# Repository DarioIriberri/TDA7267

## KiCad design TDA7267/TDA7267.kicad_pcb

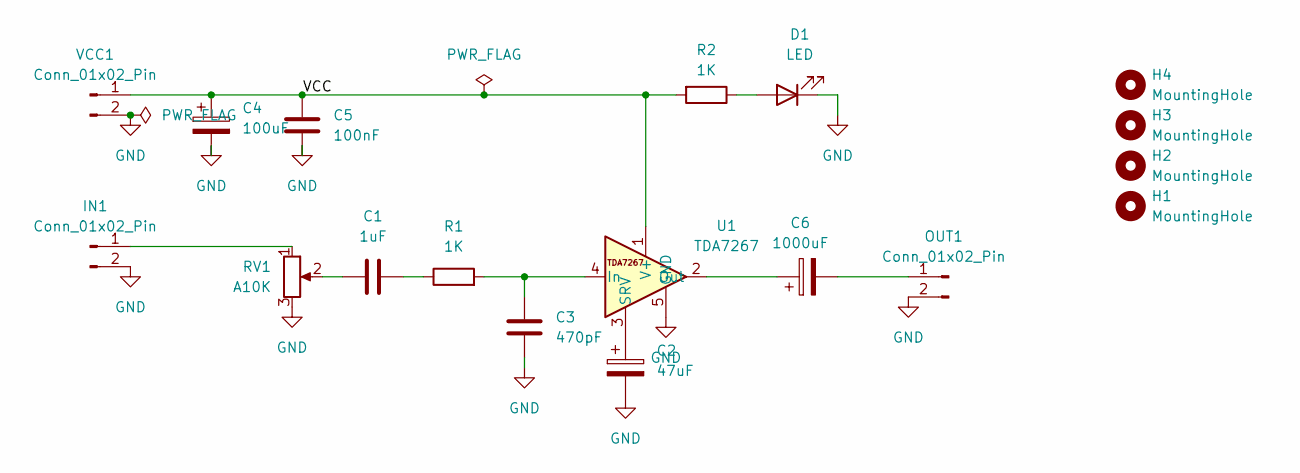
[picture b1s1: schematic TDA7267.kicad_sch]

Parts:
C1: 1uF; C_Rect_L7.2mm_W3.5mm_P5.00mm_FKS2_FKP2_MKS2_MKP2
C2: 47uF; CP_Radial_D8.0mm_P3.80mm
C3: 470pF; C_Disc_D6.0mm_W2.5mm_P5.00mm
C4: 100uF; CP_Radial_D8.0mm_P3.80mm
C5: 100nF; C_Disc_D6.0mm_W2.5mm_P5.00mm
C6: 1000uF; CP_Radial_D10.0mm_P5.00mm
D1: LED; LED_D5.0mm
H1, H2, H3, H4: MountingHole; MountingHole_2.2mm_M2
IN1: Conn_01x02_Pin; TerminalBlock_bornier-2_P5.08mm
OUT1: Conn_01x02_Pin; TerminalBlock_bornier-2_P5.08mm
R1, R2: 1K; R_Axial_DIN0207_L6.3mm_D2.5mm_P7.62mm_Horizontal
RV1: A10K; Potentiometer_Piher_T-16H_Single_Horizontal
U1: TDA7267; DIP-8_W7.62mm_LongPads
VCC1: Conn_01x02_Pin; TerminalBlock_bornier-2_P5.08mm

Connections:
/VCC: C4.1, C5.2, R2.2, U1.1 (V+), VCC1.1
GND: C2.2, C3.1, C4.2, C5.1, D1.1 (K), IN1.2, OUT1.2, RV1.3, U1.5 (GND), U1.6 (GND), U1.7 (GND), U1.8 (GND), VCC1.2
unnamed: C1.1, RV1.2
unnamed: C1.2, R1.1
unnamed: D1.2 (A), R2.1
unnamed: IN1.1, RV1.1
unnamed: C6.2, OUT1.1
unnamed: C3.2, R1.2, U1.4 (In)
unnamed: C6.1, U1.2 (Out)
unnamed: C2.1, U1.3 (SRV)

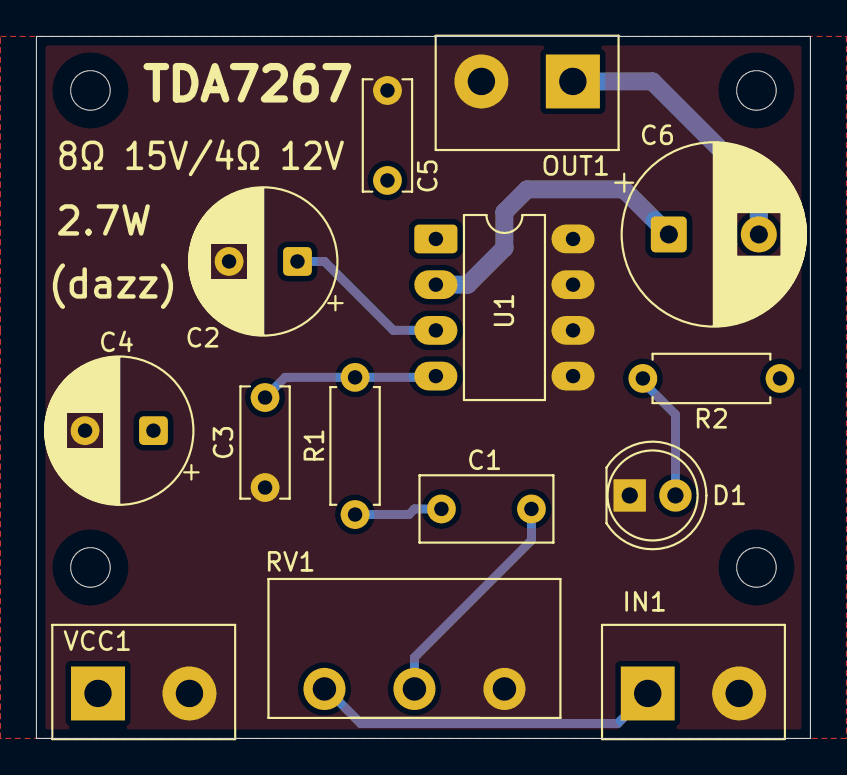
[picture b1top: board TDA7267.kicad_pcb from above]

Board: 2 copper layers, 43.0 x 39.0 mm, 18 parts (0 on the bottom side), 10 nets.

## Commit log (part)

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2025-08-28 .gitignore
2025-08-28 Improvements
2025-08-28 Tweaks
2025-08-29 More stuff
2025-09-13 Bottom GND plane
